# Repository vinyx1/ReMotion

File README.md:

# ReMotion

A seated reach trainer for people recovering from a stroke. Two small motion sensors notice when
the body leans in to do the arm's work, a buzzer says so in the moment, and a therapist sees every
reach afterwards.

ECE 198, University of Waterloo, Group 19, for CCCARE.

**Live site:** [remotion-rehab.up.railway.app](https://remotion-rehab.up.railway.app). The landing page,
and the dashboard with a 1-hour demo account (no sign-up).

## Why we built it

After a stroke, many people can't move their arm as far as they used to. So when they reach for a
cup, they lean their chest forward and let the trunk cover the distance. Therapists call this
*compensation*. It works, which is the problem: the arm never gets the practice, and the lean turns
into a habit that's hard to undo.

In the clinic, a therapist catches it and says "sit back". At home there's nobody watching, and
the usual rehab scores only ask whether the reach was completed, not how. We wanted something a
patient could use at their kitchen table that does the therapist's job for that one thing: notice
the lean, say so right away, and keep a record.

Research says this is possible with cheap sensors. Studies with a wrist and a trunk sensor picked
out leaned reaches about 9 times in 10 ([Ranganathan et al., 2017](https://doi.org/10.1088/1361-6579/aa9835);
[Seo et al., 2024](https://doi.org/10.3390/s24020554);
[Gabler et al., 2026](https://arxiv.org/abs/2604.12591)). In our team's first test, ReMotion
agreed with a blind label from side-view video on **12 of 13 reps**. Our target is 9 in 10 over more
reps and testers, and
[`docs/TESTING.md`](docs/TESTING.md) is how we measure it.

## What we built

Three pieces that work together.

**The device.** A mat with a white HOME button and three coloured target buttons, a yellow START
button, a buzzer, and two motion sensors: one on a chest strap, one on the wrist. The patient sits
up straight for 3 seconds so it learns what "upright" means for them. Then a target lights up,
they reach for it, and come back to HOME. If the chest tilts more than 10° for longer than 0.2 s,
that reach counts as leaned. The 10° can be raised for someone whose normal posture already sits a
little forward (app Settings → Lean limit).

| The electronics, inside the box | Putting it together |
|---|---|
|  |  |

A session is the same for every exercise: **3 reaches without the buzzer, 10 with it, 3 without
again.** The first three show how they move on their own. The middle ten are the training, where
the buzzer sounds whenever they lean. The last three show whether it stuck once the buzzer goes
quiet.

**The phone app** (Android). The phone props up on the table, plugs into the device, and coaches
the patient in large type that's readable from arm's length. It also sends every reach to the
dashboard over Wi-Fi.

| Get set up and choose the exercise | One instruction at a time |
|---|---|
|  |  |
| **When they lean** (buzzer block only) | **At the end** |
|  |  |

There are four exercises: reach forward, reach to the right, hand to mouth, and forearm rotation.
Forward and sideways reach work end to end on the device. Hand to mouth and forearm rotation are in
the app and dashboard, but the firmware that detects those reps is still being built, so for now
they run on the app's demo device. Settings has a Demo mode with short scripted runs for showing the
buzzer off. If calibration fails because a sensor stopped answering (a loose cable), the app says
so and asks you to replug the device.

**The dashboard** (web). Where the therapist follows each patient: how often they lean, whether
that's going down, at which targets, and a short written summary.

### Rep replay

Any single reach can be played back in 3D from the recorded sensor data, with the trunk-lean and
wrist-speed traces beside it. The trunk turns warm when it passes the limit.

| Forward reach | Hand to mouth |
|---|---|
|  |  |

The patient overview and the replays above use simulated data, made to build and test the dashboard. The exercise page shows real sessions recorded with the device during team testing.

## How it fits together

```mermaid
flowchart TB
    subgraph DEV["On the table"]
        direction LR
        S1[Chest sensor] --> A
        S2[Wrist sensor] --> A
        B[Mat buttons] --> A
        A[Arduino<br/>reach_tracker.ino] --> Z[Buzzer and<br/>button lights]
    end
    A <-- "USB serial: text lines out,<br/>commands in" --> P[Phone app]
    A <-. "or USB to a laptop" .-> L[Python logger]
    subgraph SRV["Dashboard server (Node)"]
        direction LR
        R[Raw lines] --> PL[Python logger] --> C[(CSV files)] --> E[Python export] --> J[sessions.json]
    end
    P -- "Wi-Fi, every line" --> R
    L --> C
    J -- "/api/sessions, every 5 s" --> UI[Dashboard in the browser<br/>React]
    UI <-- "Generate summary,<br/>through the server" --> CL[Claude]
```

- **The Arduino decides.** It reads both sensors 100 times a second, runs the session, judges
  every reach and sounds the buzzer itself. Nothing it does depends on the phone or the laptop,
  so the feedback never lags.
- **Everything else listens.** The Arduino prints plain text lines: one per reach (`R`), one
  status line (`I`), and live samples (`D`) for the replay. The phone and the laptop logger read
  the same lines and can send a few one-letter commands back (start, stop, plan, lean limit). The
  format is in [`docs/PROTOCOL.md`](docs/PROTOCOL.md).
- **The dashboard reads files.** The server saves the phone's lines as they arrive, runs the
  same Python logger the laptop uses to turn them into CSV files, then a Python export gathers
  every session into one `sessions.json` per account. The dashboard fetches it every 5 seconds,
  so a new reach shows up within a few seconds. A laptop recording joins the same CSV files.
- **Summaries come from Claude.** "Generate summary" sends a patient's numbers to Claude through
  the server, and the short written overview comes back.

### Hardware

| Part | Job |
|---|---|
| Arduino UNO R4 Minima | Reads the sensors and buttons, runs the session, drives the lights and buzzer |
| 2× MPU-6050 (GY-521) | Motion sensors. Chest: how far the trunk tilts. Wrist: when the arm moves |
| Adafruit 757 level shifter | Lets the 5 V Arduino talk to the 3.3 V sensors |
| 5× 30 mm lit arcade buttons | START (D2), then HOME, GREEN, BLUE, RED (D3–D6) |
| 5× 2N3904 transistors | Switch the button lights and the buzzer, which need more current than a pin gives |
| Buzzer | The only feedback during a reach |

Both sensors share one I2C bus. The wrist sensor's AD0 pin is tied high, so it answers at 0x69
and the chest sensor at 0x68. One cable runs from the mat to the wrist board (which carries the
level shifter) and on to the chest. KiCad files are in [`hardware/kicad/`](hardware/kicad/), and
there's a full-size [PDF of the schematic](docs/imu-reach-tracker-schematic.pdf).

## Run it

You need Python 3, Node 24, and for the device, the Arduino IDE or `arduino-cli`.

**Just the dashboard, with simulated patients** (no hardware):

```bash
python3 -m venv .venv && .venv/bin/pip install -r requirements.txt
.venv/bin/python -m software.dashboard.fake_history     # makes three simulated patients
cd software/web && npm install
node server/set-owner.ts you@example.com                # your login; prints a password once
npm run dev
```

Open http://localhost:5173 for the landing page, or http://localhost:5173/dashboard to sign in.
New laptop recordings in `data/` show up on the dashboard by themselves within a few seconds.
"Try a 1-hour demo" on the sign-in page works without an account. Summaries need an
`ANTHROPIC_API_KEY` in `software/web/.env`; everything else works without one.

**The device:**

1. Install the **Arduino UNO R4 Boards** package and the **Adafruit MPU6050** library.
2. Upload `firmware/reach_tracker/reach_tracker.ino`
   (`arduino-cli compile --upload --fqbn arduino:renesas_uno:minima -p <port> firmware/reach_tracker`).
3. Strap on the sensors, sit up straight, press the yellow START button. Three beeps mean the
   session is done.

To record a session on a laptop instead of the phone: `.venv/bin/python -m software.tools.logger`.
`./demo.sh` runs the short demos from the terminal.

**The phone app:**

```bash
cd software/android && ./gradlew installRelease     # with the phone plugged in and USB debugging on
```

No cable? On the dashboard (the live site, or your own), open a patient's
**Profile & settings → Connect a phone → Don't have the app?** and scan that code with the
phone's camera. Then scan the pairing code with the app, and the phone records as that patient.
With the live site the phone only needs internet.

For a dashboard on your laptop, the phone must be able to reach it: run it with `npx vite --host`
and open it at the laptop's network address rather than `localhost`. Campus Wi-Fi blocks this; a
phone hotspot works. [`docs/HANDOFF.md`](docs/HANDOFF.md) walks through the whole setup, and
[`docs/MANUAL.md`](docs/MANUAL.md) covers running a session step by step.

**Deploying:** the repo-root `Dockerfile` builds the whole dashboard server (site, API and the
Python tools it runs), and `railway.json` deploys it on Railway, which redeploys on every push to
`main`. It needs a volume at `/data`; the steps are in the
[web README](software/web/README.md#deploy-railway).

## In this repo

| Folder | What's there |
|---|---|
| `firmware/reach_tracker/` | The Arduino program |
| `software/android/` | The phone app (Kotlin, Jetpack Compose) |
| `software/web/` | Landing page, dashboard and its server ([README](software/web/README.md)) |
| `software/tools/`, `software/dashboard/` | Python: logger, protocol parser, fake data, export |
| `software/analysis/` | Validation: label sheets and threshold sweeps |
| `release/` | The current phone app (`ReMotion.apk`), which the dashboard offers for download |
| `hardware/` | Schematic, perfboard layout, enclosures, mat |
| `docs/` | Protocol, manual, testing plan, research notes, team status |

Working on the code? Read [`AGENTS.md`](AGENTS.md) first, and run
`git config core.hooksPath .githooks` once in your clone: it refuses any commit that contains an API
key, a password or a key file (CI checks every commit too).

## Team

[Vincent Jiang](https://github.com/vinyx1) ·
[Yousuf Hamoda](https://github.com/Yousuf-Hamoda) ·
[Preston Baichoo](https://github.com/prestonbaichoo3) ·
[Ali Hadi](https://github.com/Ali-Hadi123)

A student prototype, tested only on team members. Not a medical device. The 10° limit is a
starting point that still needs a clinician's eye, and the sensors can't see the trunk twisting,
only tipping forward or sideways.

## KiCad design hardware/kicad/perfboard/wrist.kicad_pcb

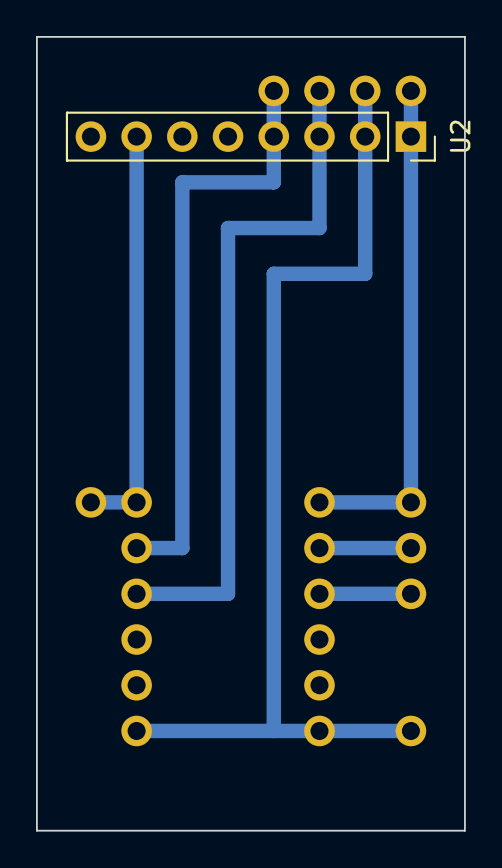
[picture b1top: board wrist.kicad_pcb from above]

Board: 2 copper layers, 23.8 x 44.1 mm, 4 parts (0 on the bottom side), 7 nets.

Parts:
J4: Cable from mat
J5: Cable to chest
U2: GY-521 wrist (0x69); PinSocket_1x08_P2.54mm_Vertical
U3: Adafruit 757 (on 2x6 female header)

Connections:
+3V3: J4.m3V3, U2.7, U3.LV
+5V: J4.m5V, J5.c5V, U2.1, U3.HV
GND: J4.mGND, J5.cGND, U2.2, U3.GND
SCL_3V3: J5.cSCL, U2.3, U3.A2
SCL_5V: J4.mSCL, U3.B2
SDA_3V3: J5.cSDA, U2.4, U3.A1
SDA_5V: J4.mSDA, U3.B1

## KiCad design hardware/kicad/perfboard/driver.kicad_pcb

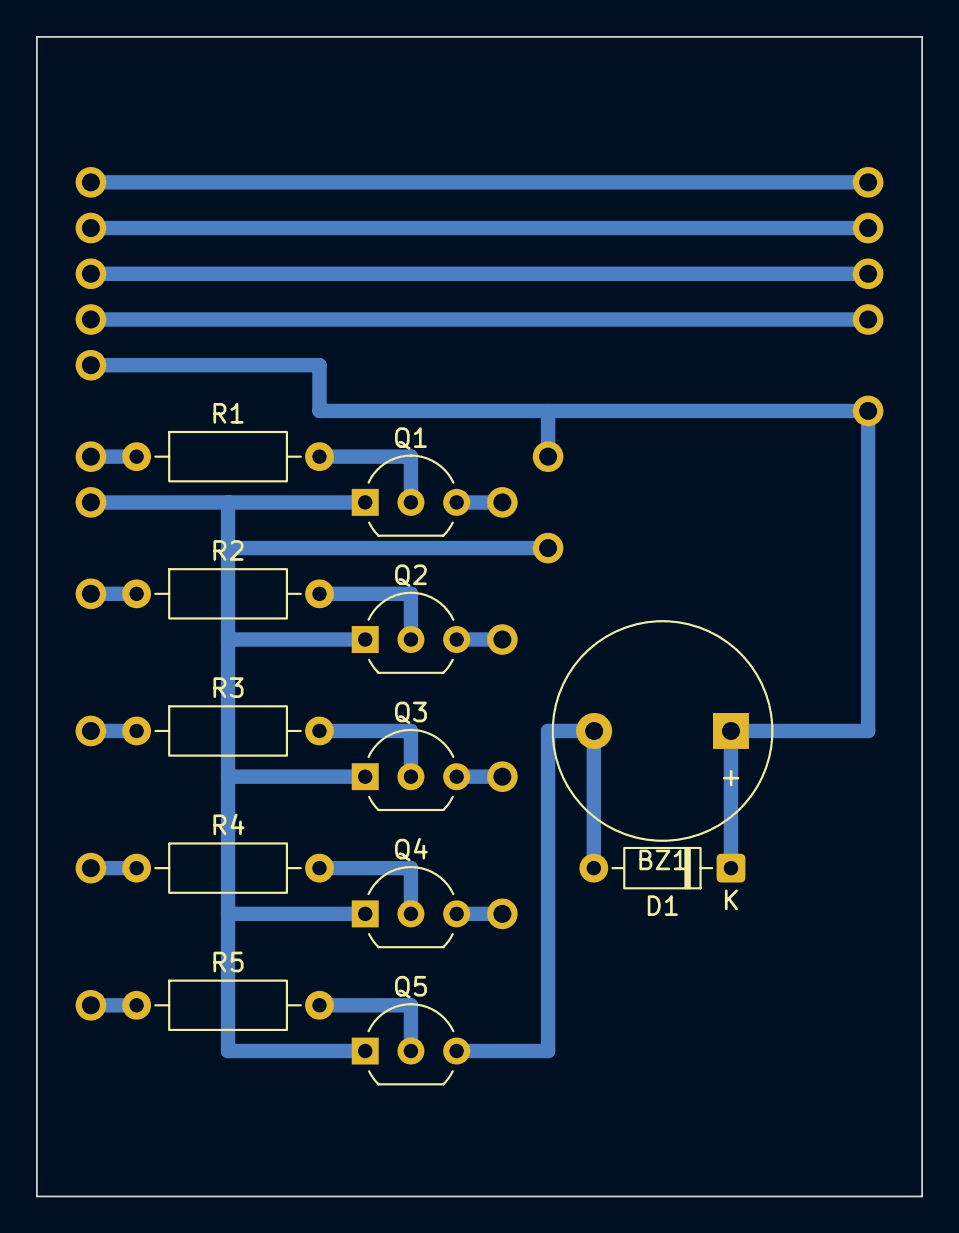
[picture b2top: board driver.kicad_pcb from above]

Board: 2 copper layers, 49.2 x 64.4 mm, 15 parts (0 on the bottom side), 20 nets.

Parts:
A1: Arduino jumper wires
BZ1: CMI-1295-0585T; Buzzer_12x9.5RM7.6
D1: 1N4148; D_DO-35_SOD27_P7.62mm_Horizontal
J2: Cable to wrist
J3: Arcade button harness
Q1, Q2, Q3, Q4, Q5: 2N3904; TO-92_Inline_Wide
R1, R2, R3, R4, R5: 1k; R_Axial_DIN0207_L6.3mm_D2.5mm_P10.16mm_Horizontal

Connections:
+3V3: A1.3V3, J2.3V3
+5V: A1.5V, BZ1.1, D1.1, J2.VCC, J3.5V
BLUE_LED_K: J3.KB, Q3.3
BUZZER_NEG: BZ1.2, D1.2, Q5.3
D9_BUZZER: A1.D9, R5.1
D10_HOME_LED: A1.D10, R1.1
D11_GREEN_LED: A1.D11, R2.1
D12_BLUE_LED: A1.D12, R3.1
D13_RED_LED: A1.D13, R4.1
GND: A1.GND, J2.GND, J3.GND, Q1.1, Q2.1, Q3.1, Q4.1, Q5.1
GREEN_LED_K: J3.KG, Q2.3
HOME_LED_K: J3.KH, Q1.3
Q1_BASE: Q1.2, R1.2
Q2_BASE: Q2.2, R2.2
Q3_BASE: Q3.2, R3.2
Q4_BASE: Q4.2, R4.2
Q5_BASE: Q5.2, R5.2
RED_LED_K: J3.KR, Q4.3
SCL_5V: A1.SCL, J2.SCL
SDA_5V: A1.SDA, J2.SDA
